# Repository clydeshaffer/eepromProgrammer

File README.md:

# eepromProgrammer
tools for loading data onto 64kbit ROMs with arduino

includes arduino firmwares, client app, and a C program for preshuffling address bits

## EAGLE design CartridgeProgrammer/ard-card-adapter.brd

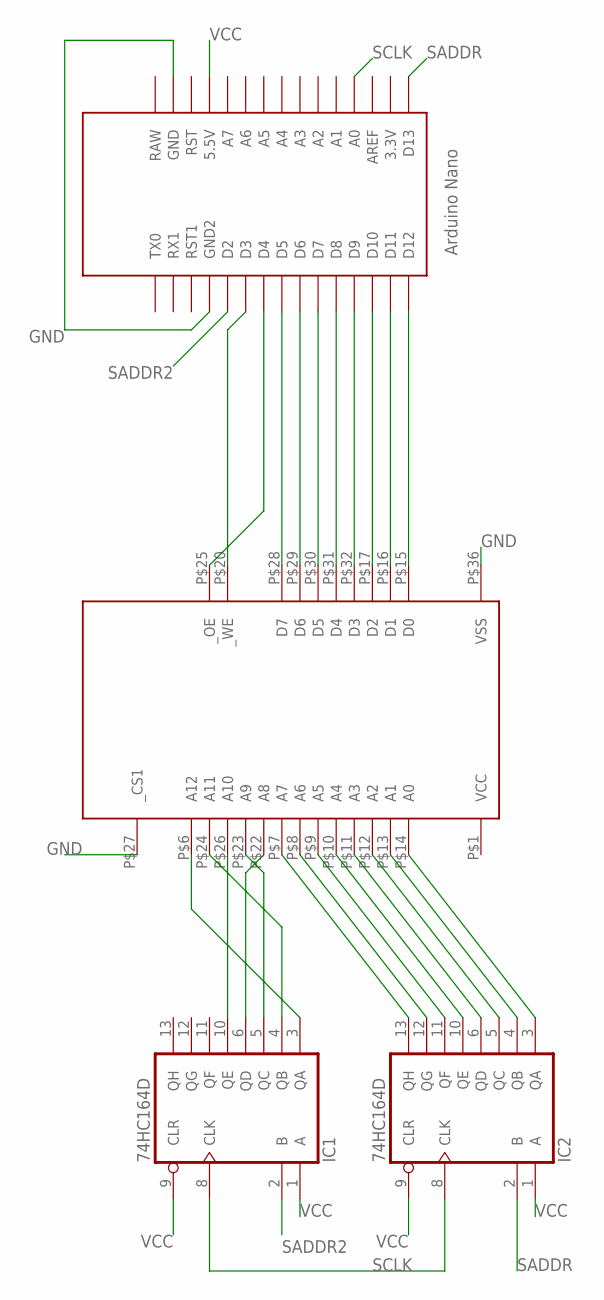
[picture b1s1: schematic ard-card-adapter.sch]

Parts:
IC1, IC2: 74HC164D; SO14
U$1: NANO
U$2: 28C64SLOT; SLOT36

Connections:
GND: IC1.7 (GND), IC2.7 (GND), U$1.GND, U$1.GND1 (GND2), U$2.P$27 (_CS1), U$2.P$36 (VSS)
unnamed: U$1.D12, U$2.P$15 (D0)
unnamed: U$1.D11, U$2.P$16 (D1)
unnamed: U$1.D10, U$2.P$17 (D2)
unnamed: U$1.D9, U$2.P$32 (D3)
unnamed: U$1.D8, U$2.P$31 (D4)
unnamed: U$1.D7, U$2.P$30 (D5)
unnamed: U$1.D6, U$2.P$29 (D6)
unnamed: U$1.D5, U$2.P$28 (D7)
unnamed: U$1.D4, U$2.P$25 (_OE)
unnamed: U$1.D3, U$2.P$20 (_WE)
unnamed: IC2.13 (QH), U$2.P$7 (A7)
unnamed: IC2.3 (QA), U$2.P$14 (A0)
unnamed: IC2.4 (QB), U$2.P$13 (A1)
unnamed: IC2.5 (QC), U$2.P$12 (A2)
unnamed: IC2.6 (QD), U$2.P$11 (A3)
unnamed: IC2.10 (QE), U$2.P$10 (A4)
unnamed: IC2.11 (QF), U$2.P$9 (A5)
unnamed: IC2.12 (QG), U$2.P$8 (A6)
unnamed: IC1.3 (QA), U$2.P$6 (A12)
unnamed: IC1.4 (QB), U$2.P$24 (A11)
unnamed: IC1.5 (QC), U$2.P$23 (A9)
unnamed: IC1.6 (QD), U$2.P$22 (A8)
unnamed: IC1.10 (QE), U$2.P$26 (A10)
SADDR: IC2.2 (B), U$1.D13
SADDR2: IC1.2 (B), U$1.D2
SCLK: IC1.8 (CLK), IC2.8 (CLK), U$1.A0
VCC: IC1.1 (A), IC1.9 (CLR), IC1.14 (VCC), IC2.1 (A), IC2.9 (CLR), IC2.14 (VCC), U$1.5V (5.5V), U$2.P$1 (VCC)

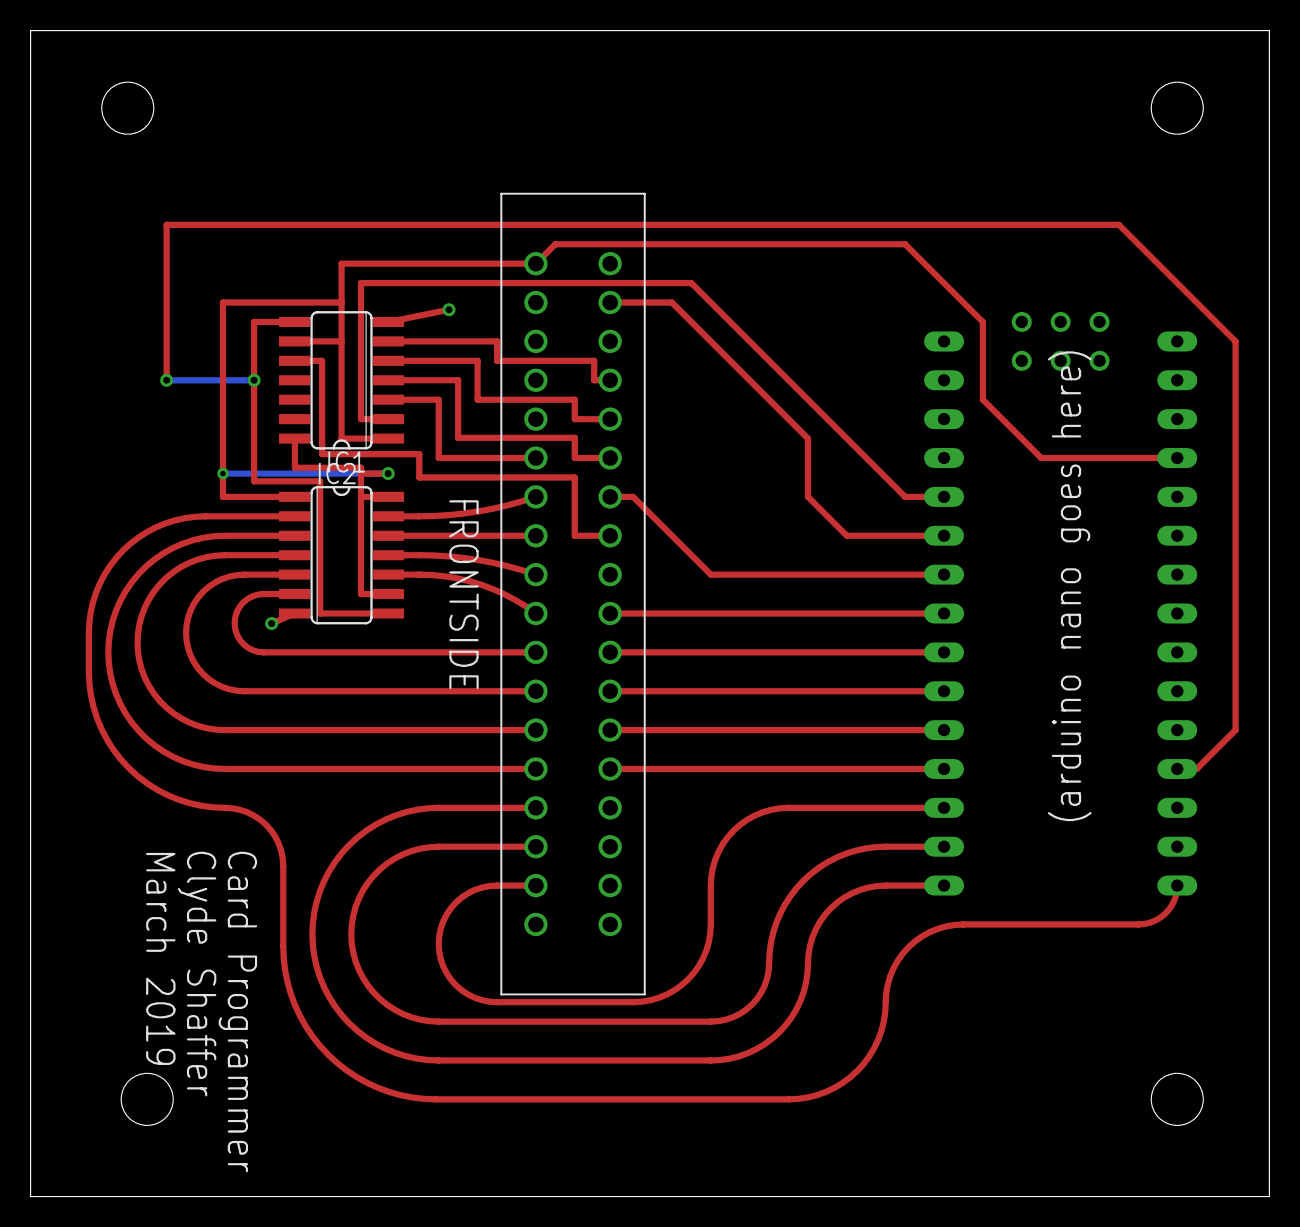
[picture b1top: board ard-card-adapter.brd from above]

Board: 2 copper layers, 81.0 x 76.2 mm, 4 parts (0 on the bottom side), 28 nets.

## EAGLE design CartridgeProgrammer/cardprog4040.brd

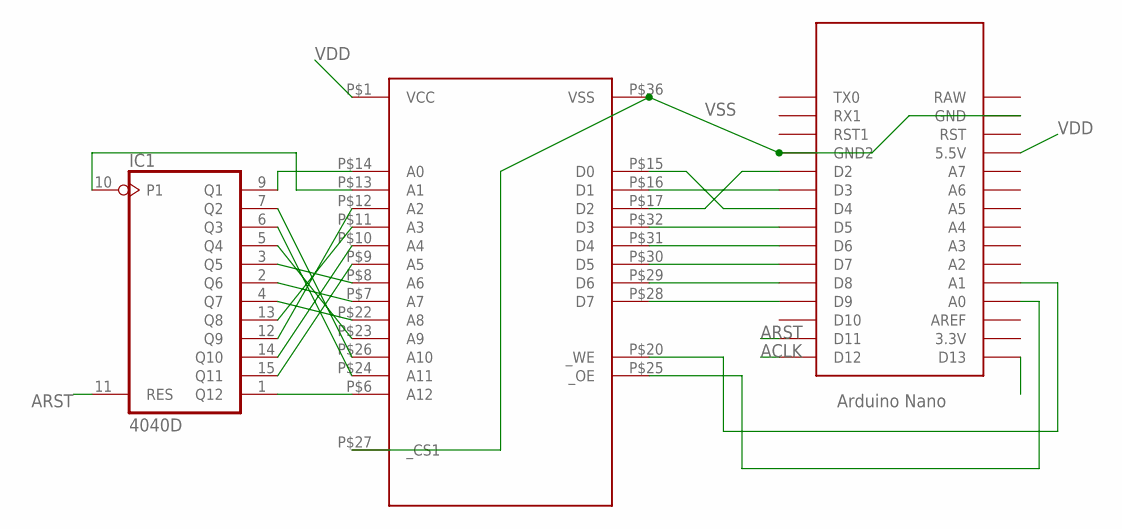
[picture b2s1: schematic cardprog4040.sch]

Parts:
IC1: 4040D; SO16
U$1: NANO
U$2: 28C64SLOT; SLOT36

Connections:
ACLK: IC1.10 (P1), U$1.D12, U$2.P$13 (A1)
ARST: IC1.11 (RES), U$1.D11
unnamed: U$1.A1, U$2.P$20 (_WE)
unnamed: U$1.D4, U$2.P$15 (D0)
unnamed: U$1.D3, U$2.P$16 (D1)
unnamed: U$1.D2, U$2.P$17 (D2)
unnamed: U$1.D5, U$2.P$32 (D3)
unnamed: U$1.D6, U$2.P$31 (D4)
unnamed: U$1.D7, U$2.P$30 (D5)
unnamed: U$1.D8, U$2.P$29 (D6)
unnamed: U$1.D9, U$2.P$28 (D7)
unnamed: U$1.A0, U$2.P$25 (_OE)
unnamed: IC1.7 (Q2), U$2.P$26 (A10)
unnamed: IC1.6 (Q3), U$2.P$24 (A11)
unnamed: IC1.5 (Q4), U$2.P$23 (A9)
unnamed: IC1.4 (Q7), U$2.P$22 (A8)
unnamed: IC1.3 (Q5), U$2.P$8 (A6)
unnamed: IC1.2 (Q6), U$2.P$7 (A7)
unnamed: IC1.1 (Q12), U$2.P$6 (A12)
unnamed: IC1.15 (Q11), U$2.P$9 (A5)
unnamed: IC1.14 (Q10), U$2.P$10 (A4)
unnamed: IC1.13 (Q8), U$2.P$11 (A3)
unnamed: IC1.12 (Q9), U$2.P$12 (A2)
unnamed: IC1.9 (Q1), U$2.P$14 (A0)
VDD: IC1.16 (VDD), U$1.5V (5.5V), U$2.P$1 (VCC)
VSS: IC1.8 (VSS), U$1.GND, U$1.GND1 (GND2), U$2.P$27 (_CS1), U$2.P$36 (VSS)

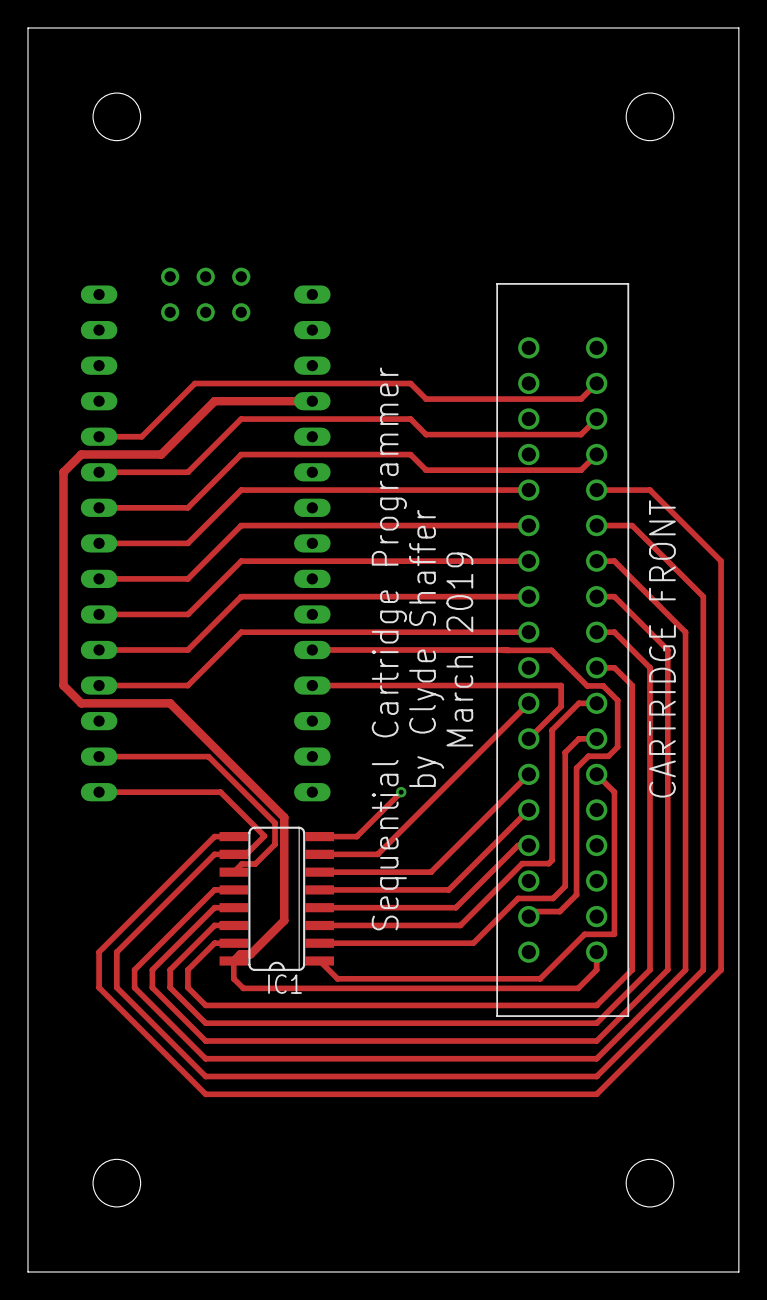
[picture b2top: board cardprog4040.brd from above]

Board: 2 copper layers, 50.8 x 88.9 mm, 3 parts (0 on the bottom side), 26 nets.

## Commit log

2019-04-25 add prescrambler utility for nonlinear loader
    v2 programmer hardware uses a 4040 counter instead of shift registers to control the address pins from the Arduino. The new PCB was designed for hardware simplicity rather than maintaining the same b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
2019-04-25 Upload arduino source for programmer hardware
    /eepromtool contains the firmware for use with a pair of shift registers, and supports arbitrary address jumping
    /eepromtool-v2 is for the version that uses a 4040 counter, which can only access addresses in a strange bit-juggled order
2019-04-25 adding EAGLE project for cartridge programmer
2019-06-07 automatic bmp header remover and usage text for scrambler
2020-07-19 change output to use percent progress
2021-01-27 arduino firmware and client script for flash cartridge programmer
2021-01-31 add better arg parsing to flashtool and a bunch of features
2021-01-31 send mode f in read mode if not eeprom mode
2021-01-31 fix bug in checksum command
2021-01-31 add test suite for newly built flash carts
2021-06-27 Update flashtool for newer node version or something
2022-03-29 Bump minimist from 1.2.5 to 1.2.6 in /flashtool
    Bumps [minimist](https://github.com/substack/minimist) from 1.2.5 to 1.2.6.
    - [Release notes](https://github.com/substack/minimist/releases)
    - [Commits](https://github.com/substack/minimist/compare/1.2.5...1.2.6)
    ---
    updated-dependencies:
    - dependency-name: minimist
2022-08-06 upgrade baud rate
2022-08-06 Bump simple-get from 3.1.0 to 3.1.1 in /flashtool
    Bumps [simple-get](https://github.com/feross/simple-get) from 3.1.0 to 3.1.1.
    - [Release notes](https://github.com/feross/simple-get/releases)
    - [Commits](https://github.com/feross/simple-get/compare/v3.1.0...v3.1.1)
    ---
    updated-dependencies:
    - dependency-name: simple-get
2022-12-31 SRAM cart compatibility
2023-06-24 Bump semver and @serialport/bindings in /flashtool
    Bumps [semver](https://github.com/npm/node-semver) and [@serialport/bindings](https://github.com/serialport/node-serialport). These dependencies needed to be updated together.
    Updates `semver` from 5.7.1 to 7.5.3
    - [Release notes](https://github.com/npm/node-semver/releases)
    - [Changelog](https://github.com/npm/node-semver/blob/main/CHANGELOG.md)
    - [Commits](https://github.com/npm/node-semver/compare/v5.7.1...v7.5.3)
    Updates `@serialport/bindings` from 9.1.0 to 9.2.9
2023-07-12 Bump semver from 5.7.1 to 5.7.2 in /flashtool
    Bumps [semver](https://github.com/npm/node-semver) from 5.7.1 to 5.7.2.
    - [Release notes](https://github.com/npm/node-semver/releases)
    - [Changelog](https://github.com/npm/node-semver/blob/v5.7.2/CHANGELOG.md)
    - [Commits](https://github.com/npm/node-semver/compare/v5.7.1...v5.7.2)
    ---
    updated-dependencies:
2024-03-26 Update eepromtool-v3.ino
    Use data polling instead of ready signal to determine when erase is complete
2024-10-14 add AVR64DA64 port
2025-12-05 Switchable bit order for flash banks
2026-03-03 default to normal flash mode
2026-03-03 fix test tool, add selftest, and test confirmation override argument
